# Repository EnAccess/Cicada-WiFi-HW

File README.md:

<p align="center">
  
</p>
<p align="center">
    <em>IoT Communications Module for Energy Access. A quick way to get production ready, bi-directional communications for your IoT embedded device.</em>
</p>
<p align="center">

</p>

---

# Cicada-WiFi-HW

Cicada WiFi HW - IoT Communications Module for Energy Access.
An easy way to get production ready, bi-directional communications for your IoT embedded device.

This repository contains the hardware design for supported Cicada wifi. This HW is designed to operate with host running cicada-FW. <https://github.com/EnAccess/Cicada-FW>

## Manufacturing files

If you are only interested in manufacturing the PCBs, you only need files in the /manufacturing/ directory. send them to your contract manufacturer of choice,Some examples of other turnkey PCBA manufacturers are:

| Manufacturers |
|---------------|
| JLCPCB |
| PCBCart |
| Bittele |

you can also get a plug and play module (might require manual FW update) from <https://www.seeedstudio.com/Enaccess-Okra-Cicada-Wifi-Communication-PCBA-p-5421.html?queryID=b07d6b6f6e1a3ef37c510602683a5443&objectID=5421&indexName=bazaar_retailer_products>.

The /manufacturing/production directory contains the PCB Gerber/drill files, the BOM, and assembly instructions.

## Source files

If you'd like to take a look at the schematics and PCB layout, first, make sure you have a fresh version of KiCAD. It's a free and open source electronics design tool,
and can be downloaded from <http://kicad.org>. Make sure you are not using an old version that some Linux distributions might be still shipping.

## File structure

The schematics and related files live under the /design/ directory:

| Directory | Content |
|-------|---------------|
| /design/doc/datasheets/ | Datasheets for some of the components used. These files are not covered by this project's open source licence |
| /design/doc/Schematic | Schematics exported as PDF. |
| /design/source/kicad/ | Kicad source files for the CICADA WIFI hardware inculding component lib files and bom generation script |
| /manufacturing/gerber/ |  these are set of files which gives information on different layers used in the project (copper layers, silk screen , court yard and other relevent files) |
| /manufacturing/stackup/ | Text file containing the details of the PCB material and stackup |
| /manufacturing/pick and place/ | Pick and place files describing component locations and orientations for PCB Assembly |
| /manufacturing/nc drill/ | NC Drill files describing type and specification of PCB drill holes (vias, through holes, mounting holes etc) |
| /manufacturing/BOM/ | BOM contains the imformation of all the components used in WiFi cicad. directely generated from Kicad using the bom genration script  |

## A quick look at the schematics

The schematics is based on ESP-07S ESP8266 Serial WiFi Module, The module supports standard IEEE802.11 b/g/n agreement, complete TCP/IP protocol stack and capable of
+20dBm output power in 802.11b mode. For more information the data sheet of the module will be available in /design/doc/datasheets/ directory

## Host interface

The Cicada uses a 2x10 female pin socket that fits perfectly in a 2x8 shrouded pin header on the host side. (We don’t use a 2x8 female pin socket because it is possible to
do a off-by-one insertion with it). The host interface provides a way for the host to detect the presence of a Cicada board,transmit and receive data, and distinguish
between different Cicada communications boards (Cicada 2g, Cicada 4g):

| Pin | Discription |
|-------|---------------|
| Pin-1   Vref(3v3) | Logic level VCC reference provided by host. only used for VER_1/2 as described below. Other cicadas Vref may be used for level shifiting for I/O pins |
| Pin-2   VER_1 | Board version pin (represents, what type of cicada it is 2g,4g or WiFi), for more information please check schematics |
| Pin-3   GND |  |
| Pin-4   VER_2 | Board version pin (represents, latest production release version) |
| Pin-5   5V | 5v Power provided by host. Peak curent consuption <200mA |
| Pin-6   GND |  |
| Pin-7   GND |  |
| Pin-8   POWER_EN | Drive high to enable power |
| Pin-9   NC |  |
| Pin-10   NC |  |
| Pin-11   NC |  |
| Pin-12 UART_Tx_3V3 | Should be connected to host's UART_TX |
| Pin-13 UART_Rx_3V3 | Should be connected to host's UART_RX |
| Pin-14   MODE_SELECT |  Pull low to Enable ESP-8266 FW flashing mode, |
| Pin-15   NC |  |
| Pin-16 n_RESET| drive low to reset, drive at 1.8 - 3.3v during normal operation |

## Power

Board is powered up by single-chip SMPS (HX3406) to convert 5v down to 3.3v required by ESP-07S(ESP8266 Serial WiFi Module WiFi module).

## Antenna

The ESP-07S ESP8266 Serial WiFi Module has a on board IPEX connector, which can be extended to an antenna using U.FL cable

## ESP8266 operating MODEs

| ESP8266 operating MODE  | GPIO15 | GPIO0 | GPIO2 |
|-------|--------|-------|-------|
| FW flashing | low | low | high |
| Normal/UART | low | high | high |

# Need to Flash the module with the latest FW??

## Requirements

- USB to serial TTL adapter hardware
- esptool.py (Ubuntu package esptool or GitHub - espressif/esptool: Espressif SoC serial bootloader utility)
- Wifi firmware: <https://www.espressif.com/sites/default/files/ap/ESP8266_NonOS_AT_Bin_V1.7.4.zip>
Note: Make sure the USB to serial adapter is set to 3.3V IO voltage! (usually there is a jumper for that)

## Setup

Connect Wifi module and USB adapter

| Cicada WiFi | USB adapter |
|-------------|--------------|
| 5V0 | 5V0 |
| GND | GND |
| POWER_EN | 3V3 |
| UART_RX_3V3 | Rx |
| UART_TX_3V3 | Tx |
| MODE_SELECT | GND |

The module should now respond to AT commands. You can check this by running the serial_linux example from Cicada.

## Flash firmware

- Unzip the firmware package and go to ESP8266_NonOS_AT_Bin_V1.7.4/bin directory. Then run this command to flash:
esptool.py -p /dev/ttyUSB0 --chip esp8266 write_flash --flash_size 4MB-c1 0x00000 boot_v1.7.bin 0x01000 at/1024+1024/user1.2048.new.5.bin 0x1fc000   esp_init_data_default_v08.bin 0xfe000 blank.bin 0x1fb000 blank.bin 0x1fe000 blank.bin

After flashing, remove the grounding of IO0(MODE_SELECT) again, so it’s free floating. The Cicada module should now be ready for installation.

# Future Improvements

- invitigate on adding an amplifier to the design for range improvemnet

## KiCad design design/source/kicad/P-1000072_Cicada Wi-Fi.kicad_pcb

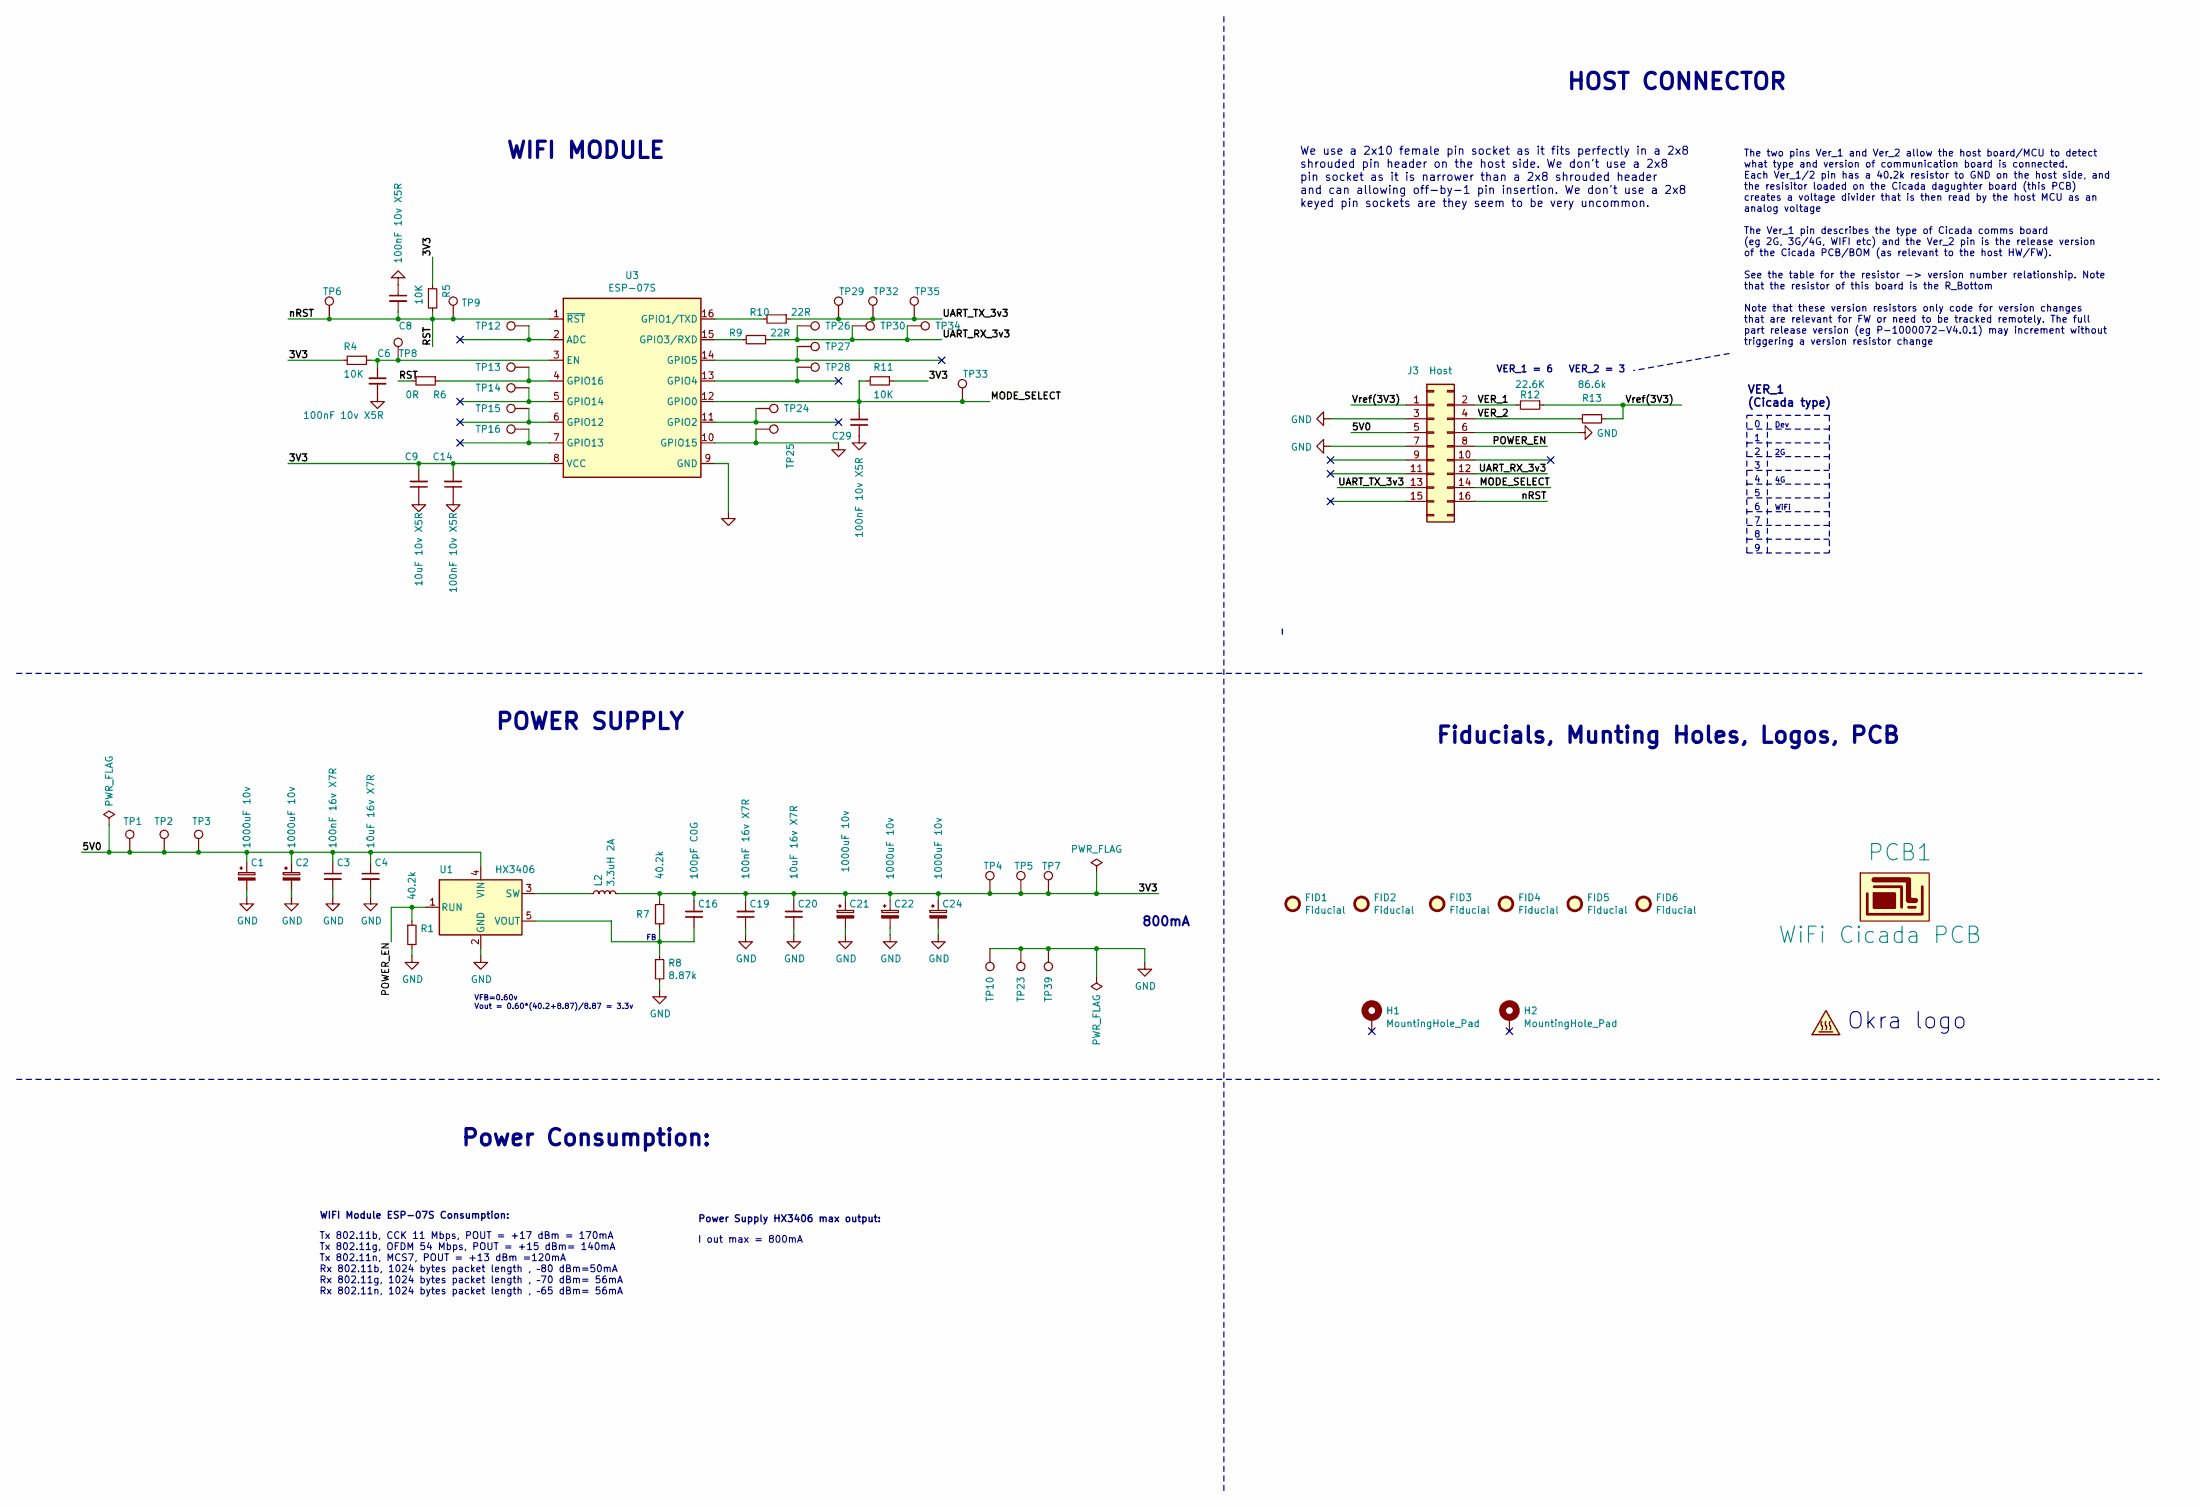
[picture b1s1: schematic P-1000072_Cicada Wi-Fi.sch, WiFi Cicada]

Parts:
C1, C2, C21, C22, C24: 1000uF 10v; CP_Radial_D8.0mm_P3.50mm; MPN GR108M010F12RR0VL4FP0
C3, C19: 100nF 16v X7R; C_0603_1608Metric; MPN 0603B104K500NT
C4, C20: 10uF 16v X7R; C_0805_2012Metric; MPN 0805B106K160NT
C6, C8, C14, C29: 100nF 10v X5R; C_0402_1005Metric; MPN CC0402MRX5R6BB104
C9: 10uF 10v X5R; C_0402_1005Metric; MPN CC0402MRX5R6BB106
C16: 100pF C0G; C_0402_1005Metric; MPN 0402CG101J500NT
FID1, FID2, FID3, FID4, FID5, FID6: Fiducial; Fiducial_1mm_Mask2mm
H1, H2: MountingHole_Pad; MountingHole_3.2mm_M3_ISO14580_Pad
J3: Host; PinSocket_2x08_P2.54mm_Vertical_padded; MPN C30867
L2: 3.3uH 2A; L_4030_Handsoldering; MPN FPI0403F-3R3M
LOGO1: SYM_Hot_Small; okra_logo_copper_2
PCB1: WiFi Cicada PCB
R1, R7: 40.2k; R_0402_1005Metric; MPN 0402WGF4022TCE
R4, R5, R11: 10K; R_0402_1005Metric; MPN 0402WGF1002TCE
R6: 0R; R_0402_1005Metric; MPN 0402WGJ0000TCE
R8: 8.87k; R_0402_1005Metric; MPN 0402WGF8871TCE
R9, R10: 22R; R_0402_1005Metric; MPN 0402WGF220JTCE
R12: 22.6K; R_0402_1005Metric; MPN 0402WGF2262TCE
R13: 86.6k; R_0402_1005Metric; MPN 0402WGF8662TCE
TP1, TP3: 5v; TestPoint_Pad_D1.5mm
TP2: 5v; TestPoint_THTPad_D1.5mm_Drill0.7mm
TP4, TP8: EN; TestPoint_Pad_D1.5mm
TP5, TP7: Vcc; TestPoint_Pad_D1.5mm
TP6, TP9: RST; TestPoint_Pad_D1.5mm
TP10, TP23, TP39: GND; TestPoint_Pad_D1.5mm
TP12: ADC; TestPoint_Pad_D1.5mm
TP13: P16; TestPoint_Pad_D1.5mm
TP14: P14; TestPoint_Pad_D1.5mm
TP15: P12; TestPoint_Pad_D1.5mm
TP16: P13; TestPoint_Pad_D1.5mm
TP24: P02; TestPoint_Pad_D1.5mm
TP25: P15; TestPoint_Pad_D1.5mm
TP26, TP30, TP34: Rx; TestPoint_Pad_D1.5mm
TP27: AMP_EN; TestPoint_Pad_D1.5mm
TP28: P4; TestPoint_Pad_D1.5mm
TP29, TP32, TP35: Tx; TestPoint_Pad_D1.5mm
TP33: P0; TestPoint_Pad_D1.5mm
U1: HX3406; TSOT-23-5; MPN HX3406
U3: ESP-07S; MPN ESP-07S

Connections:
/3V3: C9.2, C14.2, C16.1, C19.1, C20.1, C21.1, C22.1, C24.1, L2.2, R4.2, R5.1, R7.1, R11.1, TP4.1, TP5.1, TP7.1, U3.8 (VCC)
/5V0: C1.1, C2.1, C3.1, C4.1, J3.5, TP1.1, TP2.1, TP3.1, U1.4 (VIN); also elsewhere on the board
/MODE_SELECT: C29.2, J3.14, R11.2, TP33.1, U3.12 (GPIO0)
/POWER_EN: J3.8, R1.1, U1.1 (RUN)
/RST: C8.2, J3.16, R5.2, R6.2, TP6.1, TP9.1, U3.1 (~RST)
/UART_RX_3v3: J3.12, R9.1, TP26.1, TP30.1, TP34.1
/UART_TX_3v3: J3.13, R10.1, TP29.1, TP32.1, TP35.1
/VER_1: J3.2, R12.2
/VER_2: J3.4, R13.2
/Vref(3V3): J3.1, R12.1, R13.1
GND: C1.2, C2.2, C3.2, C4.2, C6.1, C8.1, C9.1, C14.1, C19.2, C20.2, C21.2, C22.2, C24.2, C29.1, J3.3, J3.6, J3.7, R1.2, R8.2, TP10.1, TP23.1, TP25.1, TP39.1, U1.2 (GND), U3.9 (GND), U3.10 (GPIO15); also elsewhere on the board
unnamed: C6.2, R4.1, TP8.1, U3.3 (EN)
unnamed: C16.2, R7.2, R8.1, U1.5 (VOUT)
unnamed: L2.1, U1.3 (SW)
unnamed: R6.1, TP13.1, U3.4 (GPIO16)
unnamed: R9.2, U3.15 (GPIO3/RXD)
unnamed: R10.2, U3.16 (GPIO1/TXD)
unnamed: TP12.1, U3.2 (ADC)
unnamed: TP14.1, U3.5 (GPIO14)
unnamed: TP15.1, U3.6 (GPIO12)
unnamed: TP16.1, U3.7 (GPIO13)
unnamed: TP24.1, U3.11 (GPIO2)
unnamed: TP27.1, U3.14 (GPIO5)
unnamed: TP28.1, U3.13 (GPIO4)

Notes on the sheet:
The two pins Ver_1 and Ver_2 allow the host board/MCU to detect what type and version of communication board is connected. Each Ver_1/2 pin has a 40.2k resistor to GND on the host side, and the resisitor loaded on the Cicada dagughter board (this PCB) creates a voltage divider that is then read by 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
Dev
WiFi
VER_1 (Cicada type)
Okra logo
VER_1 = 6
VER_2 = 3
We use a 2x10 female pin socket as it fits perfectly in a 2x8 shrouded pin header on the host side. We don't use a 2x8 pin socket as it is narrower than a 2x8 shrouded header and can allowing off-by-1 pin insertion. We don't use a 2x8 keyed pin sockets are they seem to be very uncommon.
VFB=0.60v Vout = 0.60*(40.2+8.87)/8.87 = 3.3v
POWER SUPPLY
Power Consumption:
Tx 802.11b, CCK 11 Mbps, POUT = +17 dBm = 170mA Tx 802.11g, OFDM 54 Mbps, POUT = +15 dBm= 140mA Tx 802.11n, MCS7, POUT = +13 dBm =120mA Rx 802.11b, 1024 bytes packet length , –80 dBm=50mA Rx 802.11g, 1024 bytes packet length , –70 dBm= 56mA Rx 802.11n, 1024 bytes packet length , –65 dBm= 56mA
WIFI MODULE
WIFI Module ESP-07S Consumption:
Power Supply HX3406 max output:
800mA
I out max = 800mA
HOST CONNECTOR
Fiducials, Munting Holes, Logos, PCB

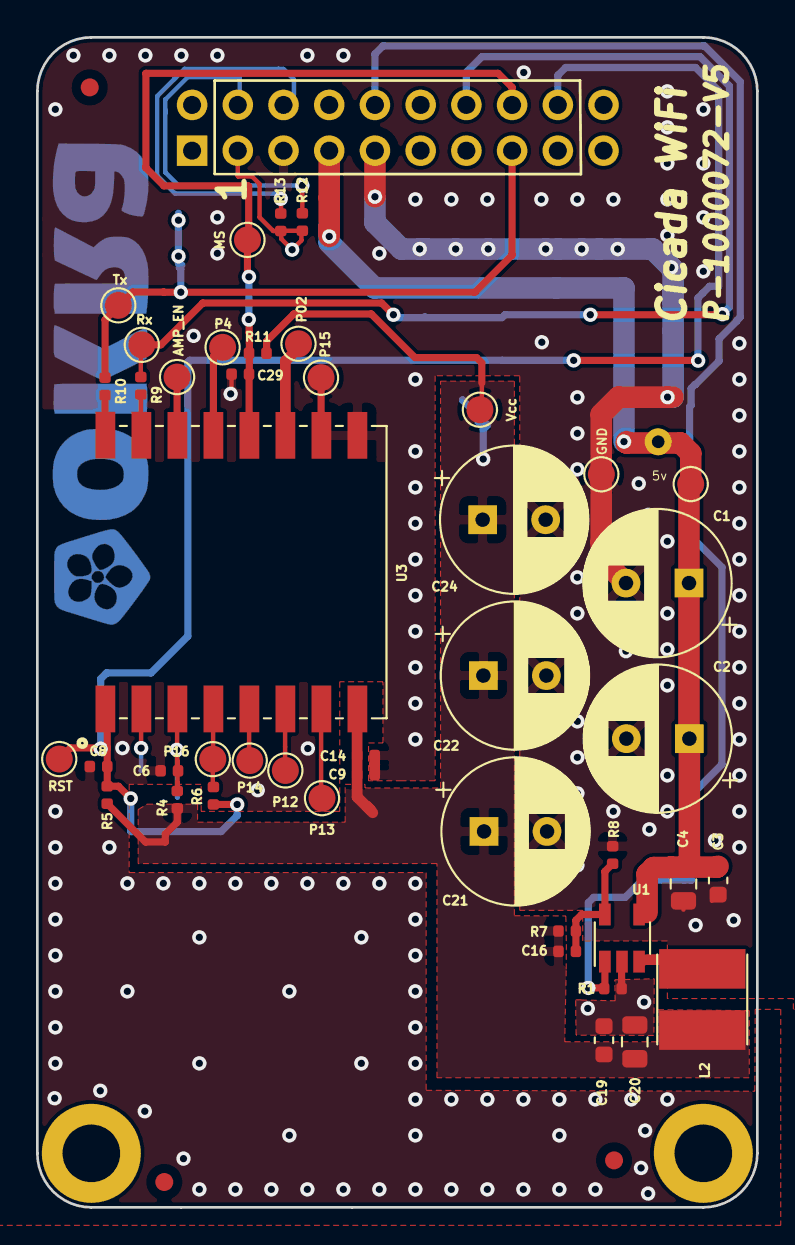
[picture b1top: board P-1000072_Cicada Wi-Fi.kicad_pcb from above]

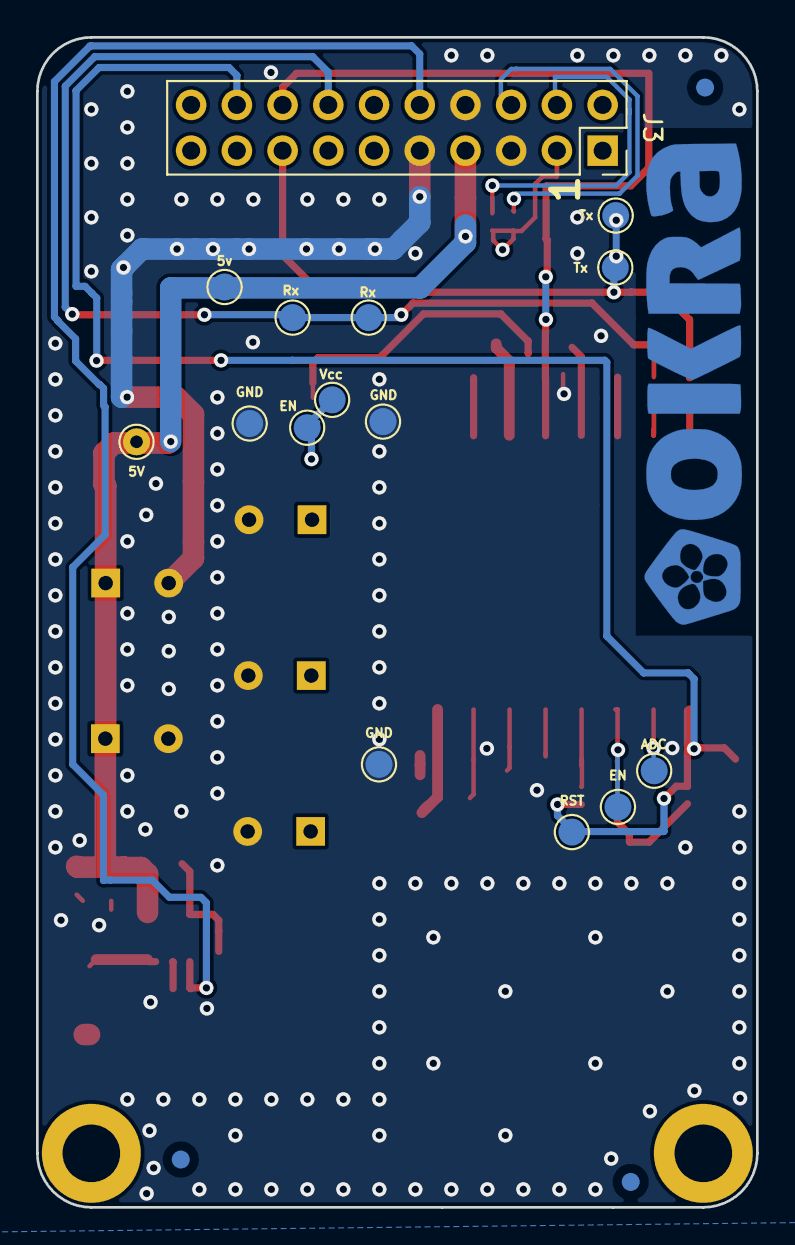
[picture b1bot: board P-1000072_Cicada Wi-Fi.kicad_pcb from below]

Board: 2 copper layers, 40.0 x 65.0 mm, 68 parts (19 on the bottom side), 24 nets.

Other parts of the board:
5V: 5v; TestPoint_THTPad_D1.5mm_Drill0.7mm
TP39#2: GND; TestPoint_Pad_D1.5mm

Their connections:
/5V0: 5V.1; also elsewhere on the board
GND: TP39#2.1; also elsewhere on the board

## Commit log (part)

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2021-11-02 First Commit WiFi Cicada HW design and manufacturing Files
2021-11-03 Revert "Initial commit"
    This reverts commit a872841a291728a75ed3f95c8ef4e7cdddd3d2e0.
2021-11-03 WiFi Cicada First Design and Manufacturing files release
2021-12-24 updated design and manufacturing file version 4.0.0
2021-12-24 created Readme.md
2022-01-06 updated readme.md
    - Added tables and titles where ever necessary
2022-01-06 deleted previous production files, reviewed SCH and PCB files
2022-01-19 1.Schematics improvement and crediblity (cleared empty spaces, improved read me and reviewed and cleaned component spec mismatch 2.PCB improments (cleaned top layer copper zones, cleaned vias and upd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
2022-01-20 v4.0.2 Design and Production File ReleaseCleaned up Top and bottom Fabrication layer, Add Bom in seed Studio formate
2022-03-30 P-1000072-V5.1.0_Cicada Wi-Fi Design and Manufacturing files update
    Design update
    1.)Inductor L2 Foot-print dimensions changed to parts commanded Foot-print dimensions(check for more information:design\doc\review\2022-03 Seed studios)
    Manufacturing update
    1.)updated manufacturing output files for the design change (L2 foot-print dimensions)
2022-04-21 Changes made: -Cleaned up README.md Files -Cleaned design/doc/datasheets removed unwanted datasheets -Cleaned design/source/ removed unwanted files -Added design/source/kicad/OKRA_bom_csv_grouped_by_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
2022-11-16 Update README.md
    updated Seed studio link
2023-10-26 Add `LICENSE`
2023-10-26 Add `markdownlint` CI
2023-10-26 Fix `README`
2023-10-26 Update CI
2023-10-26 Remove unneeded stuff
2023-10-26 Update `.yamllint`
2024-09-19 Add `CODE_OF_CONDUCT.md`
2024-09-23 Add `.github/SECURITY.md`
2024-09-23 Add `.github/PULL_REQUEST_TEMPLATE.md`
2024-09-23 Add `.github/ISSUE_TEMPLATE/config.yml`
2024-09-23 Add `.github/ISSUE_TEMPLATE/feature_request.yml`
2024-09-23 Add `.github/ISSUE_TEMPLATE/bug_report.yml`
2024-09-23 Add `CONTRIBUTING.md`
2025-04-28 Add `DISCORD_ETIQUETTE.md`
